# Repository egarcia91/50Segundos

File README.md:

# 50Segundos

Empieza el trabajo profesional

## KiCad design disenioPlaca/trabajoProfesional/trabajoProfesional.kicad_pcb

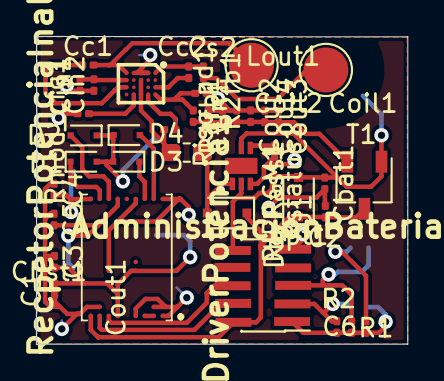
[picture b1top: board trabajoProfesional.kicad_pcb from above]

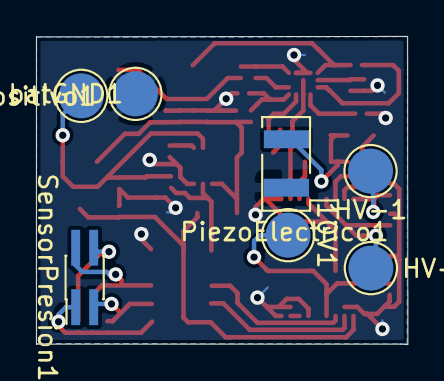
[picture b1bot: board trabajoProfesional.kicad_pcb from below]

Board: 2 copper layers, 20.6 x 17.1 mm, 47 parts (7 on the bottom side), 31 nets.

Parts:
10V1: Conn_01x01_Male; TestPoint_Pad_D2.5mm
AdministracionBateria1: SC810ULTRT; SON50P200X200X60-7N-D
BatPositivo1: Conn_01x01_Male; TestPoint_Pad_D2.5mm
C1, C2, C3, C4, C5: 10n; C_0201_0603Metric
C6: 100n; C_0201_0603Metric
Cbat1: 2.2u; C_0201_0603Metric
Cbst1: 47n; C_0201_0603Metric
Cc1, Cc2: 1n; C_0201_0603Metric
Cin1: 22u; C_0201_0603Metric
Cin2: 100n; C_0201_0603Metric
Coil1, Coil2: Conn_01x01_Male; TestPoint_Pad_D2.5mm
Cout1, Cout2, Cout3, Cout4: 22u; C_0201_0603Metric
Cs2: 10n; C_0201_0603Metric
Cvin1: 2.2u; C_0201_0603Metric
D1, D2, D3, D4: 1.8; D_SC-80
DbyPass1: D_Schottky; D_SOD-323F
DriverPotencia1: HV7360GA-G; HV7360GAG
HV+1: Conn_01x01_Male; TestPoint_Pad_D2.5mm
HV-1: Conn_01x01_Male; TestPoint_Pad_D2.5mm
Lout1: 4.7u; L_0603_1608Metric_Pad1.05x0.95mm_HandSolder
PiezoElectrico1: UTR-1440K-TT-R; PinHeader_1x02_P2.54mm_Vertical_SMD_Pin1Left
R1, R2, R2fb1: 10k; R_0201_0603Metric
R1fb1: 46k; R_0201_0603Metric
RIPRGM1: R; R_0201_0603Metric
RecpetorPotenciaInalambrica1: TS51223-M000WCSR; BGA20C40P4X5_190X230X58
Riso_pd1: R; R_0201_0603Metric
Rmod_cfg1: 60k; R_0201_0603Metric
Rstatus1: R; R_0201_0603Metric
SensorPresion1: MS583730BA01-50; PinHeader_2x02_P1.00mm_Vertical_SMD
T1: MPMOS; TSOT-23
U1: 1501; PinHeader_2x05_P1.00mm_Vertical_SMD
batGND1: Conn_01x01_Male; TestPoint_Pad_D2.5mm
opt1: D_Schottky; D_SOD-323F

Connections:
10V: 10V1.1, C1.1, C3.2, DriverPotencia1.A6, DriverPotencia1.F4
+Bat: AdministracionBateria1.5, BatPositivo1.1, Cbat1.1, Rstatus1.1, T1.1, opt1.2
+HV: C5.2, DriverPotencia1.P6, HV+1.1
-HV: C4.2, DriverPotencia1.P9, HV-1.1
/Bateria/Cargando: AdministracionBateria1.2, Rstatus1.2, U1.8
/Salida/Alimentacion: C2.1, DbyPass1.1, DriverPotencia1.A9, T1.3, U1.1, opt1.1
/Salida/SN1ONOFF: DriverPotencia1.A7, U1.4
/Salida/SP1ONOFF: DriverPotencia1.A8, U1.3
GND: AdministracionBateria1.3, C1.2, C2.2, C3.1, C4.1, C5.1, Cbat1.2, Cin1.1, Cin2.1, Cout1.1, Cout2.1, Cout3.1, Cout4.1, Cvin1.2, DriverPotencia1.A1, DriverPotencia1.A4, DriverPotencia1.B2, DriverPotencia1.B8, DriverPotencia1.F7, DriverPotencia1.P1, DriverPotencia1.P4, PiezoElectrico1.1, R2fb1.1, RIPRGM1.1, RecpetorPotenciaInalambrica1.B1, RecpetorPotenciaInalambrica1.C1, RecpetorPotenciaInalambrica1.D1, Riso_pd1.1, Rmod_cfg1.2, U1.2, batGND1.1
unnamed: AdministracionBateria1.1, Cout1.2, Cout2.2, Cout3.2, Cout4.2, Cvin1.1, DbyPass1.2, Lout1.1, R1fb1.1, Riso_pd1.2, T1.2
unnamed: AdministracionBateria1.4, RIPRGM1.2
unnamed: C6.1, SensorPresion1.4
unnamed: C6.2, R1.1, R2.1, SensorPresion1.1, U1.6
unnamed: Cbst1.1, Lout1.2, RecpetorPotenciaInalambrica1.C2, RecpetorPotenciaInalambrica1.C3, RecpetorPotenciaInalambrica1.C4
unnamed: Cbst1.2, RecpetorPotenciaInalambrica1.B4
unnamed: Cc1.1, RecpetorPotenciaInalambrica1.E3
unnamed: Cc1.2, Coil2.1, RecpetorPotenciaInalambrica1.E1
unnamed: Cc2.1, Cs2.1, RecpetorPotenciaInalambrica1.A1
unnamed: Cc2.2, RecpetorPotenciaInalambrica1.A3
unnamed: Cin1.2, Cin2.2, RecpetorPotenciaInalambrica1.E2
unnamed: Coil1.1, Cs2.2
unnamed: D1.1, DriverPotencia1.P8
unnamed: D1.2, D2.1, D3.2, D4.1, PiezoElectrico1.2
unnamed: D2.2, DriverPotencia1.P7
unnamed: D3.1, DriverPotencia1.P3
unnamed: D4.2, DriverPotencia1.P2
unnamed: DriverPotencia1.A2, DriverPotencia1.A3
unnamed: R1fb1.2, R2fb1.2, RecpetorPotenciaInalambrica1.A4
unnamed: RecpetorPotenciaInalambrica1.D4, Rmod_cfg1.1
SCLPresion: R2.2, SensorPresion1.3, U1.7
SDAPresion: R1.2, SensorPresion1.2, U1.9

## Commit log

2020-10-15 inicio unificado proyecto de 50 segundos
2020-10-15 se crean los modulos de parte de codigo
2020-10-15 bloque de senial de salida hecho, falta elegir el encodeo de la senial
2020-10-15 Muy en panales ya estan los valores que importan del sensor falta procesarlo mejor encontre un par de guias igual
2020-10-15 creado modulo de encodeo de mensaje
2020-10-15 se arregla etapa negativa
2020-10-15 Ciclo principal comienzo muy tranqui
2020-10-16 Ciclo principal incluyendo la senial de salida
2020-10-20 se hacen mas gruesas las pistas y se rellenan las areas vacias de parte frontal
2021-05-10 Change to Arduino IDE with installation guide
2021-05-11 Se agrega Lectura and senial salida
2021-05-11 Se agrega la senial de salida completa junto con el pasaje a bits
2021-05-13 un poco de prolijidad para ver mas claro el codigo
2021-06-21 Code Arduino con test transductor
2021-07-24 Sensor de presion test
2021-09-21 codigo perdido
